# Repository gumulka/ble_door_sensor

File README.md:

# Bluetooth Window/Door Sensor

A simple project to observe a window or door is open/closed.
It works like most other sensors as well. A magnet has to get attached to the door and
if it comes near the board, it is detected and the state of the window or door is updated.

## How to build

If you are new to Zephyr, read the [Getting Started Guide](https://docs.zephyrproject.org/latest/develop/getting_started/index.html).
Afterwards you can clone and build this project with:

```bash
west init -m https://github.com/gumulka/ble_door_sensor --mr main door_sensor
cd door_sensor
west update
cd ble_door_sensor
```

### Bootloader

The bootloader will load and verify the image that is executed. To make it
easier to upgrade the device, two images are saved on the device and only one is
being executed, while the other is a standby for updating. The bootloader cannot
be upgraded via ble, but the image can be. Therefore making it possible to
upgrade devices in the field.

If you have a unprogrammed device, use this to build and flash the bootloader:

```bash
west build -p -b ble_door_sensor -d build_mcuboot ../bootloader/mcuboot/boot/zephyr/ -- -DCONFIG_BOOT_SIGNATURE_TYPE_ECDSA_P256=y
west flash -d build_mcuboot
```

### Application

The application is different from the bootloader and is what is in need of
updates/upgrades.

```bash
west build -p -b ble_door_sensor app
west flash
```

It is also possible to build the application with debug output for the UART
on the backside of the board.
This is disabled by default as it has a significant influence on battery.

```bash
west build -p -b ble_door_sensor app -- -DEXTRA_CONF_FILE=="debug.conf"
```

### Energy sensor

When I wanted to integrate energy consumption into home assistant without
having to order new hardware, I soldered two resistors to the board and
converted it into an energy monitor.
A 1M Ohm between VCC and AIN0 and 22k Ohm between AIN0 and GND.
This can be configured with:

```bash
west build -p -b ble_door_sensor app -- -DEXTRA_DTC_OVERLAY_FILE=="energy-tracker.dtsi"
```

## Update via BLE

If you have an already running device and just want to upgrade to the latest
firmware.

Either with the nRF Connect App, which can be quite handy, or in the commandline
use these steps:

```bash
sudo mcumgr --conntype ble --connstring ctlr_name=hci0,peer_name='Sensor' image upload build/zephyr/zephyr.signed.bin
sudo mcumgr --conntype ble --connstring ctlr_name=hci0,peer_name='Sensor' image list
```

Use the second hash provided from the second command to alter the following:

```bash
sudo mcumgr --conntype ble --connstring ctlr_name=hci0,peer_name='Sensor' image test "HASH_FROM_OUTPUT"
sudo mcumgr --conntype ble --connstring ctlr_name=hci0,peer_name='Sensor' reset
# wait for the system to restart and if you are sure, that the update was successful then
sudo mcumgr  --conntype ble --connstring ctlr_name=hci0,peer_name='Sensor' image confirm "HASH_FROM_OUTPUT"
```

More information about the general procedure can be found [here](https://docs.zephyrproject.org/latest/samples/subsys/mgmt/mcumgr/smp_svr/README.html)
and [here](https://docs.zephyrproject.org/latest/services/device_mgmt/mcumgr.html)

> [!TIP]
> I have seen a few errors when trying to upload the image and found that it
> works best, if I cancel the upload command after a few seconds and restart it
> a few seconds later, basically splitting the upload into 4-5 chunks instead
> of uploading it as a whole.

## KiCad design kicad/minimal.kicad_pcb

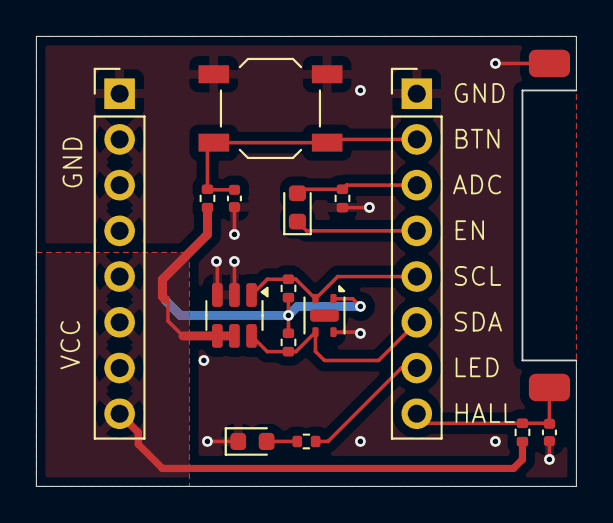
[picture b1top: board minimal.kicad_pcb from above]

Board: 2 copper layers, 30.0 x 25.0 mm, 16 parts (0 on the bottom side), 10 nets.

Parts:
C101: 10nF; C_0402_1005Metric
C102: 100nF; C_0402_1005Metric
D101: LED; LED_0603_1608Metric
J101, J102: Conn_01x08; PinHeader_1x08_P2.54mm_Vertical
Q101: ALS-PT19; LED_0603_1608Metric
R101, R106: 1K; R_0402_1005Metric
R102: 1M; R_0402_1005Metric
R103, R104, R105: 100k; R_0402_1005Metric
SW101: SW_Reed; reed_contact
SW102: SW_Push; SW_SPST_TL3342
U101: SHTC3; Sensirion_DFN-4-1EP_2x2mm_P1mm_EP0.7x1.6mm
U102: TMP100; SOT-23-6

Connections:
/BUTTON: C102.1, J102.2, R103.2, SW102.2
/HALL_SENSOR: C101.1, J102.8, R102.2, SW101.2
/LED: J102.7, R101.1
/PHOTO_ADC: J102.3, Q101.2 (E), R106.1
/PHOTO_ENABLE: J102.4, Q101.1 (C)
/SCL: J102.5, R104.2, U101.2 (SCL), U102.1 (SCL)
/SDA: J102.6, R105.2, U101.3 (SDA), U102.6 (SDA)
GND: C101.2, C102.2, D101.1 (K), J101.1, J101.2, J101.3, J101.4, J102.1, R106.2, SW101.1, SW102.1, U101.4 (VSS), U102.2 (GND), U102.3 (ADD1)
unnamed: D101.2 (A), R101.2
VCC: J101.5, J101.6, J101.7, J101.8, R102.1, R103.1, R104.1, R105.1, U101.1 (VDD), U102.4 (V+), U102.5 (ADD0)

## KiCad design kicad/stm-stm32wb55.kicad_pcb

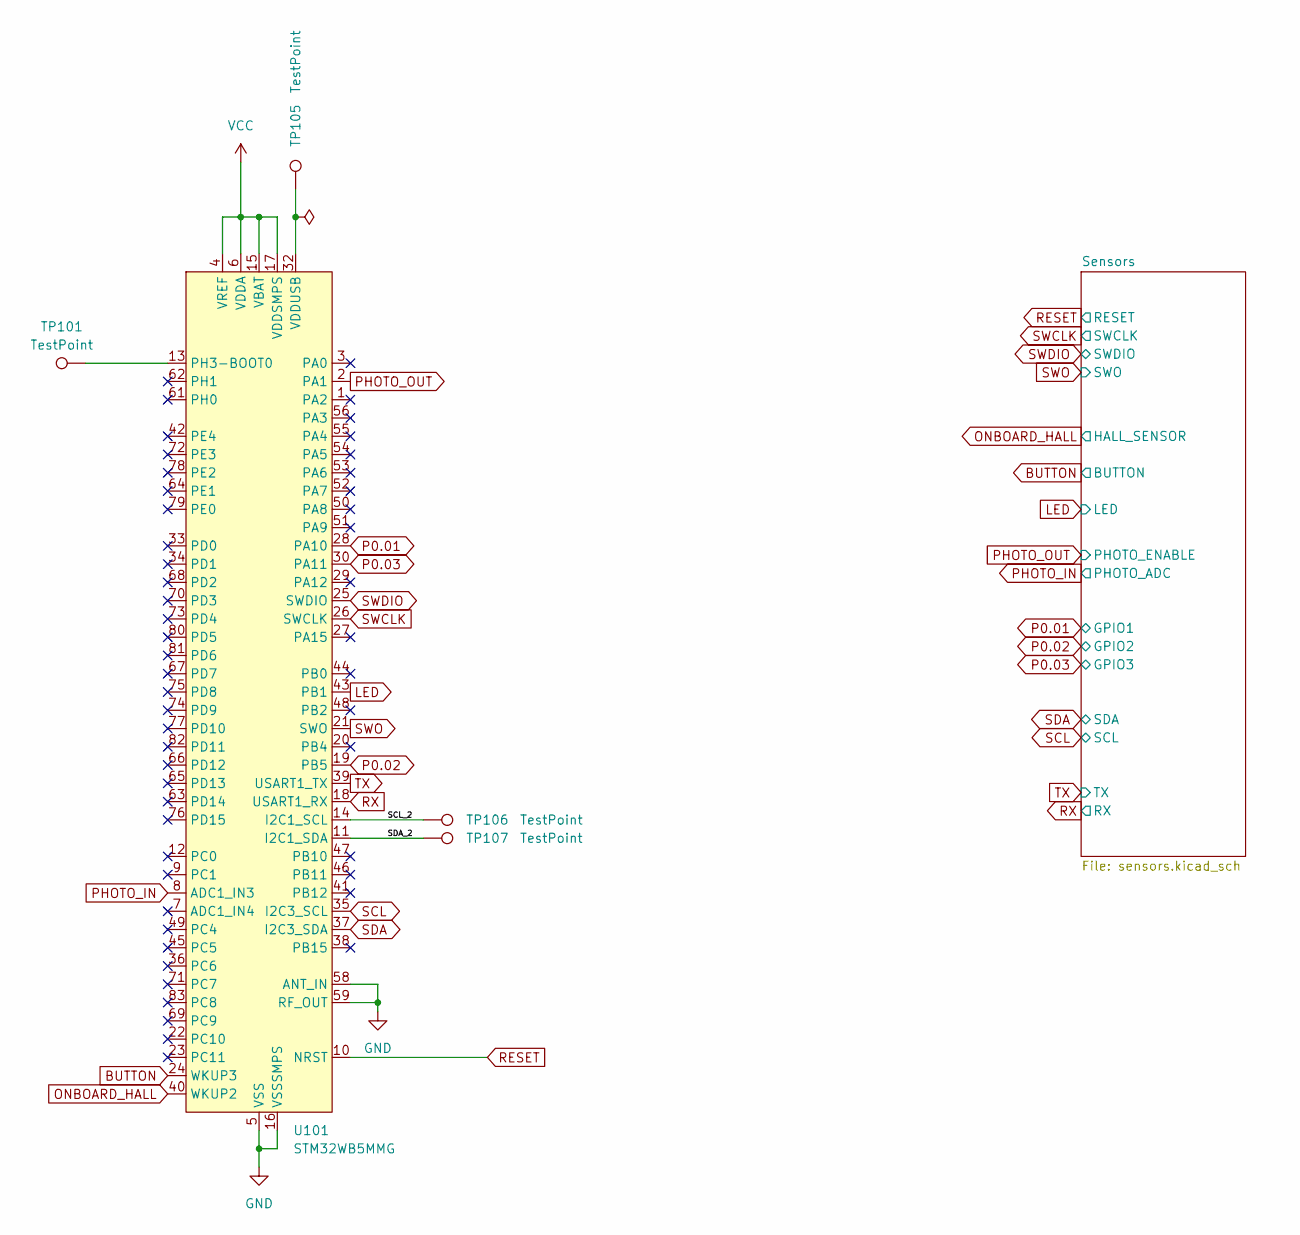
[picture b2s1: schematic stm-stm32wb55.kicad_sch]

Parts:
TP101, TP105, TP106, TP107: TestPoint; TestPoint_Pad_D1.5mm
U101: STM32WB5MMG; ST-SiP-LGA-86-11x7.3mm

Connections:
/SCL_2: TP106.1, U101.14 (I2C1_SCL)
/SDA_2: TP107.1, U101.11 (I2C1_SDA)
BUTTON: U101.24 (WKUP3); also elsewhere on the board
GND: U101.5 (VSS), U101.16 (VSSSMPS), U101.31 (VSS), U101.57 (VSS), U101.58 (ANT_IN), U101.59 (RF_OUT), U101.60 (VSS), U101.84 (VSS), U101.86 (VSS); also elsewhere on the board
LED: U101.43 (PB1); also elsewhere on the board
unnamed: TP101.1, U101.13 (PH3-BOOT0)
unnamed: TP105.1, U101.32 (VDDUSB)
ONBOARD_HALL: U101.40 (WKUP2); also elsewhere on the board
P0.01: U101.28 (PA10); also elsewhere on the board
P0.02: U101.19 (PB5); also elsewhere on the board
P0.03: U101.30 (PA11); also elsewhere on the board
PHOTO_IN: U101.8 (ADC1_IN3); also elsewhere on the board
PHOTO_OUT: U101.2 (PA1); also elsewhere on the board
RESET: U101.10 (NRST); also elsewhere on the board
RX: U101.18 (USART1_RX); also elsewhere on the board
SCL: U101.35 (I2C3_SCL); also elsewhere on the board
SDA: U101.37 (I2C3_SDA); also elsewhere on the board
SWCLK: U101.26 (SWCLK); also elsewhere on the board
SWDIO: U101.25 (SWDIO); also elsewhere on the board
SWO: U101.21 (SWO); also elsewhere on the board
TX: U101.39 (USART1_TX); also elsewhere on the board
VCC: U101.4 (VREF), U101.6 (VDDA), U101.15 (VBAT), U101.17 (VDDSMPS); also elsewhere on the board

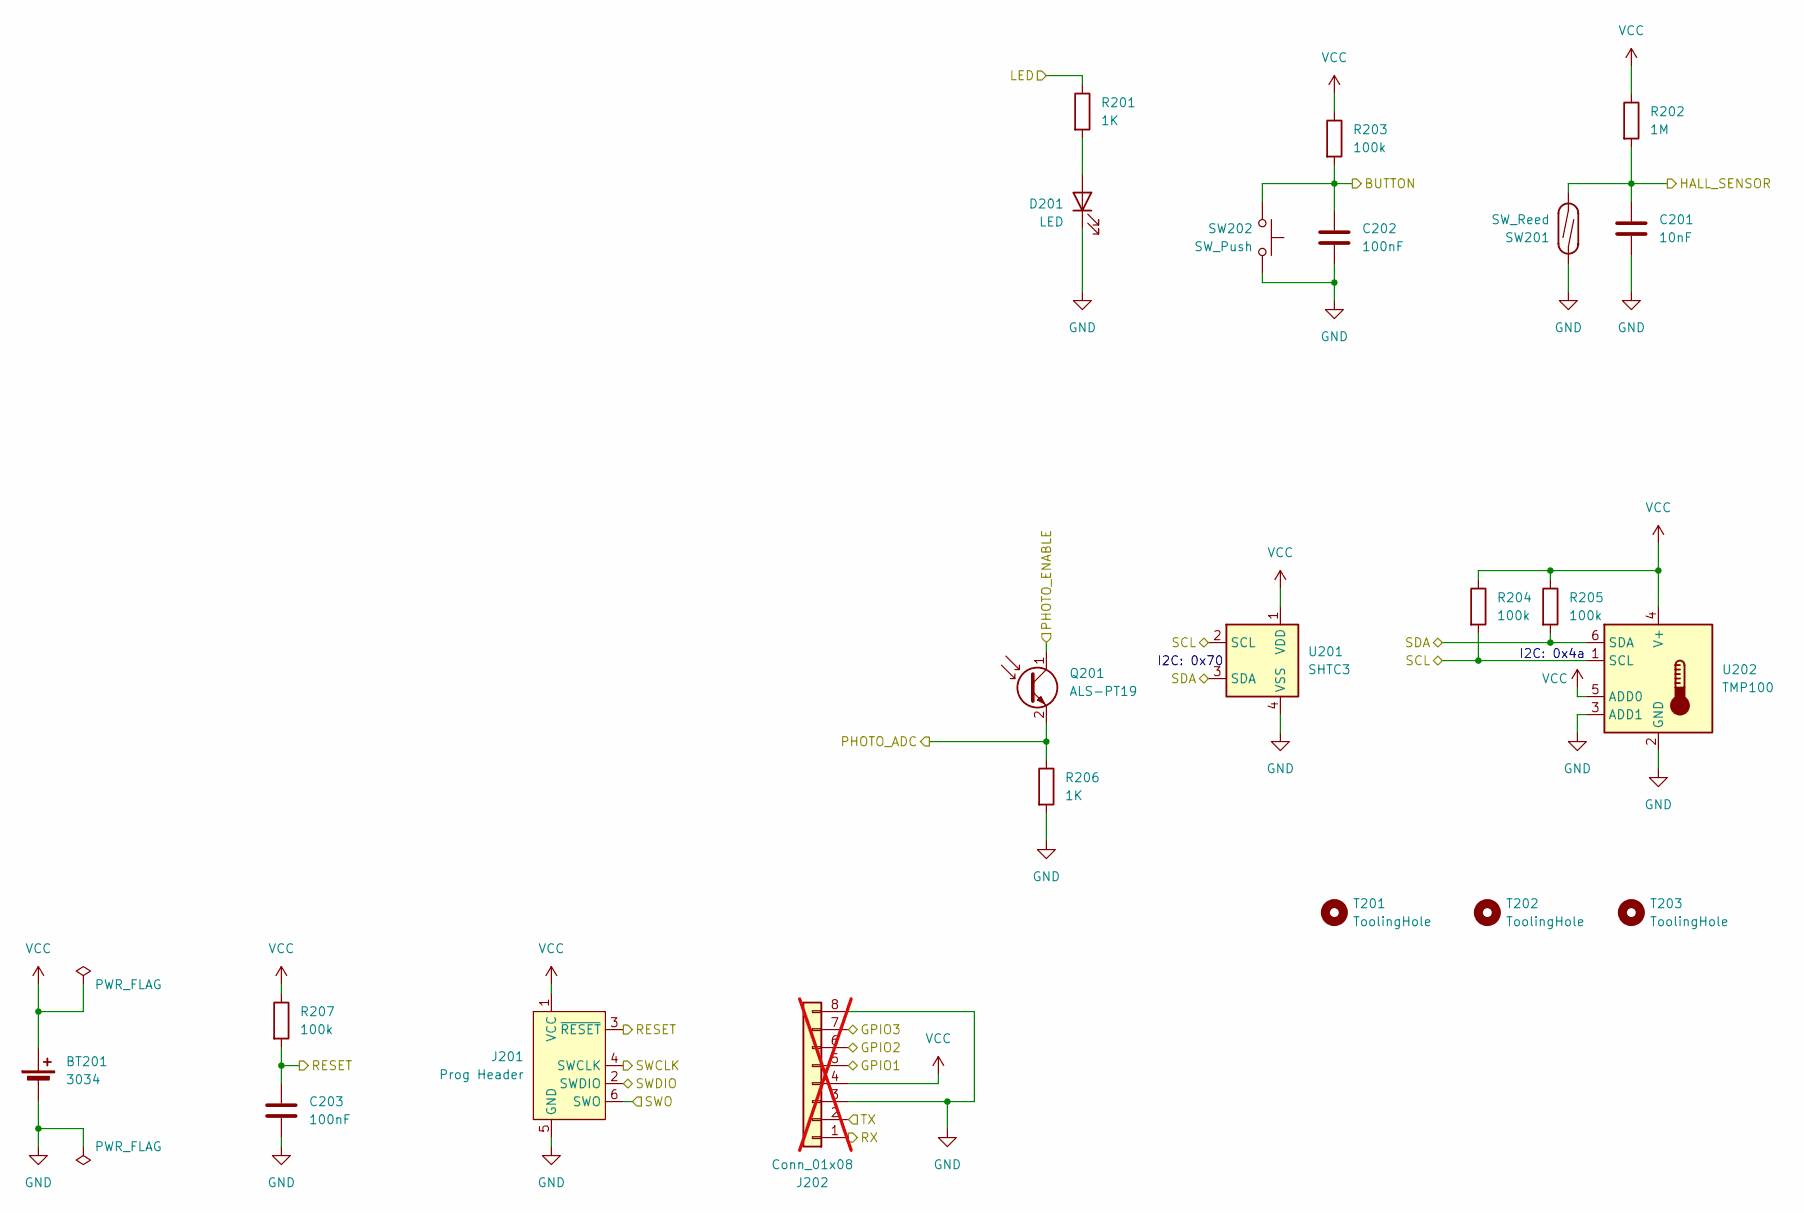
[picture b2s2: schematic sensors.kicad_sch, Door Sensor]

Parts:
BT201: 3034; BatteryHolder_Keystone_3034_1x20mm; MPN 3034TR; LCSC# C5213768
C201: 10nF; C_0402_1005Metric; MPN 10nF 0402; LCSC# C15195
C202, C203: 100nF; C_0402_1005Metric; MPN 100nF 0402; LCSC# C1525
D201: LED; LED_0603_1608Metric; MPN KP-1608SGC; LCSC# C72043
J201: Prog Header; Tag-Connect_TC2030-IDC-NL_2x03_P1.27mm_Vertical
J202: Conn_01x08; PinHeader_1x08_P2.54mm_Vertical_SMD_Pin1Left; not fitted
Q201: ALS-PT19; LED_0603_1608Metric; MPN ALS-PT19-315C/L177/TR8; LCSC# C146233
R201, R206: 1K; R_0402_1005Metric; MPN 1K; LCSC# C11702
R202: 1M; R_0402_1005Metric; MPN 1M; LCSC# C26083
R203, R204, R205, R207: 100k; R_0402_1005Metric; MPN 100K; LCSC# C25741
SW201: SW_Reed; reed_contact
SW202: SW_Push; SW_SPST_TL3342; MPN TS-1187A-B-A-B; LCSC# C318884
T201, T202, T203: ToolingHole; JLCPCB_Mounting_hole
U201: SHTC3; Sensirion_DFN-4-1EP_2x2mm_P1mm_EP0.7x1.6mm; MPN SHTC3-TR-10KS; LCSC# C2880044
U202: TMP100; SOT-23-6; MPN TMP100NA/3K; LCSC# C31810

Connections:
BUTTON: C202.1, R203.2, SW202.2; also elsewhere on the board
GND: BT201.2 (-), C201.2, C202.2, C203.2, D201.1 (K), J201.5 (GND), J202.3, J202.8, R206.2, SW201.2, SW202.1, U201.4 (VSS), U202.2 (GND), U202.3 (ADD1); also elsewhere on the board
LED: R201.1; also elsewhere on the board
unnamed: D201.2 (A), R201.2
ONBOARD_HALL: C201.1, R202.2, SW201.1; also elsewhere on the board
P0.01: J202.5; also elsewhere on the board
P0.02: J202.6; also elsewhere on the board
P0.03: J202.7; also elsewhere on the board
PHOTO_IN: Q201.2 (E), R206.1; also elsewhere on the board
PHOTO_OUT: Q201.1 (C); also elsewhere on the board
RESET: C203.1, J201.3 (~RESET), R207.2; also elsewhere on the board
RX: J202.1; also elsewhere on the board
SCL: R204.2, U201.2 (SCL), U202.1 (SCL); also elsewhere on the board
SDA: R205.2, U201.3 (SDA), U202.6 (SDA); also elsewhere on the board
SWCLK: J201.4 (SWCLK); also elsewhere on the board
SWDIO: J201.2 (SWDIO); also elsewhere on the board
SWO: J201.6 (SWO); also elsewhere on the board
TX: J202.2; also elsewhere on the board
VCC: BT201.1 (+), J201.1 (VCC), J202.4, R202.1, R203.1, R204.1, R205.1, R207.1, U201.1 (VDD), U202.4 (V+), U202.5 (ADD0); also elsewhere on the board

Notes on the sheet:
I2C: 0x4a
I2C: 0x70

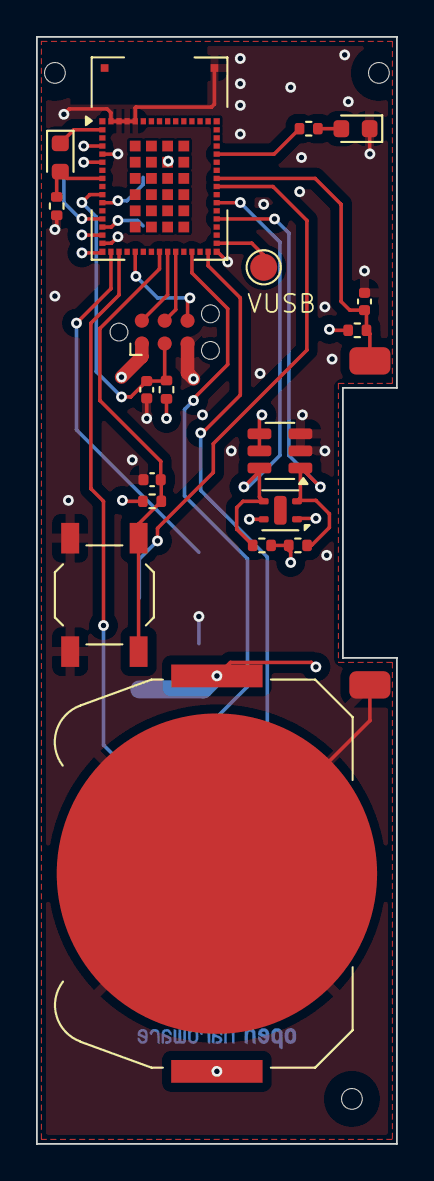
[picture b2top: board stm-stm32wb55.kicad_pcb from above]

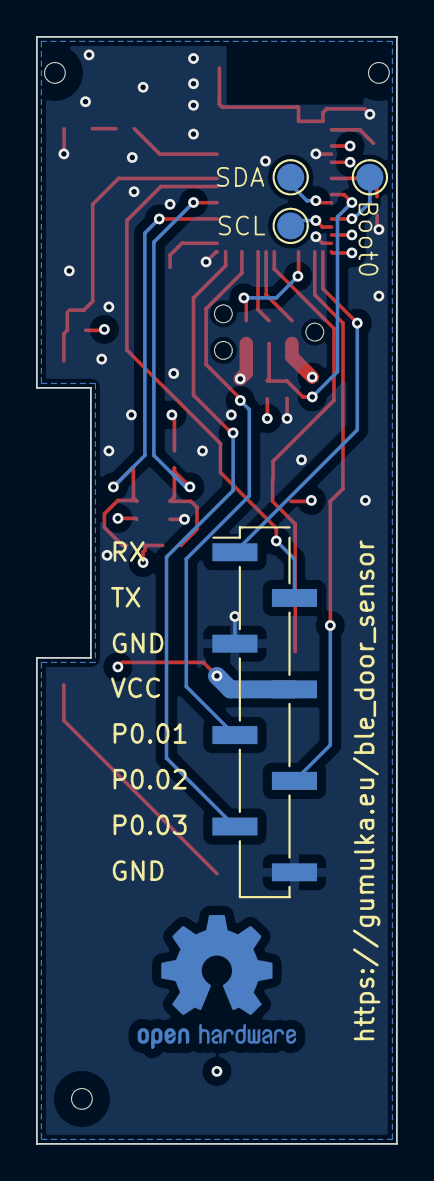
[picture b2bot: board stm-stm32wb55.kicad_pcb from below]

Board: 4 copper layers, 20.0 x 61.5 mm, 27 parts (4 on the bottom side), 23 nets.

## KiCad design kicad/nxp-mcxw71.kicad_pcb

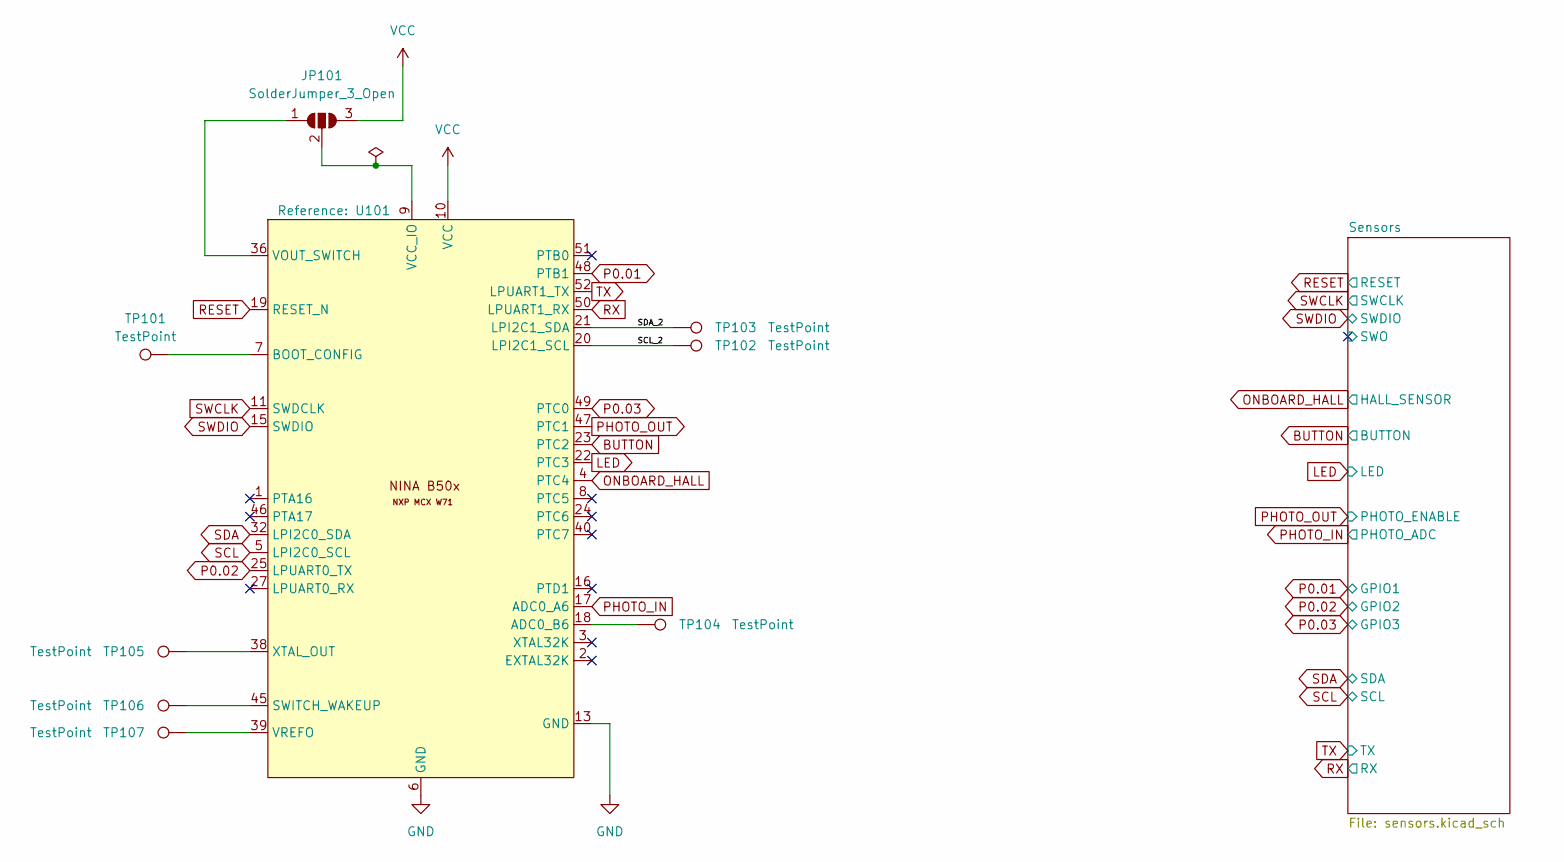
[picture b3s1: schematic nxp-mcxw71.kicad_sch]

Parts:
JP101: SolderJumper_3_Open; SolderJumper-3_P2.0mm_Open_TrianglePad1.0x1.5mm
TP101, TP102, TP103, TP104, TP105, TP106, TP107: TestPoint; TestPoint_Pad_D1.5mm
U101: NINA-B506

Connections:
/SCL_2: TP102.1, U101.20 (LPI2C1_SCL)
/SDA_2: TP103.1, U101.21 (LPI2C1_SDA)
BUTTON: U101.23 (PTC2); also elsewhere on the board
GND: U101.6 (GND), U101.12 (GND), U101.13 (GND), U101.14 (GND), U101.26 (GND), U101.30 (GND), U101.53 (GND), U101.EGP (GND); also elsewhere on the board
LED: U101.22 (PTC3); also elsewhere on the board
unnamed: JP101.1 (A), U101.36 (VOUT_SWITCH)
unnamed: JP101.2 (C), U101.9 (VCC_IO)
unnamed: TP101.1, U101.7 (BOOT_CONFIG)
unnamed: TP104.1, U101.18 (ADC0_B6)
unnamed: TP106.1, U101.45 (SWITCH_WAKEUP)
unnamed: TP107.1, U101.39 (VREFO)
unnamed: TP105.1, U101.38 (XTAL_OUT)
ONBOARD_HALL: U101.4 (PTC4); also elsewhere on the board
P0.01: U101.48 (PTB1); also elsewhere on the board
P0.02: U101.25 (LPUART0_TX); also elsewhere on the board
P0.03: U101.49 (PTC0); also elsewhere on the board
PHOTO_IN: U101.17 (ADC0_A6); also elsewhere on the board
PHOTO_OUT: U101.47 (PTC1); also elsewhere on the board
RESET: U101.19 (RESET_N); also elsewhere on the board
RX: U101.50 (LPUART1_RX); also elsewhere on the board
SCL: U101.5 (LPI2C0_SCL); also elsewhere on the board
SDA: U101.32 (LPI2C0_SDA); also elsewhere on the board
SWCLK: U101.11 (SWDCLK); also elsewhere on the board
SWDIO: U101.15 (SWDIO); also elsewhere on the board
TX: U101.52 (LPUART1_TX); also elsewhere on the board
VCC: JP101.3 (B), U101.10 (VCC); also elsewhere on the board

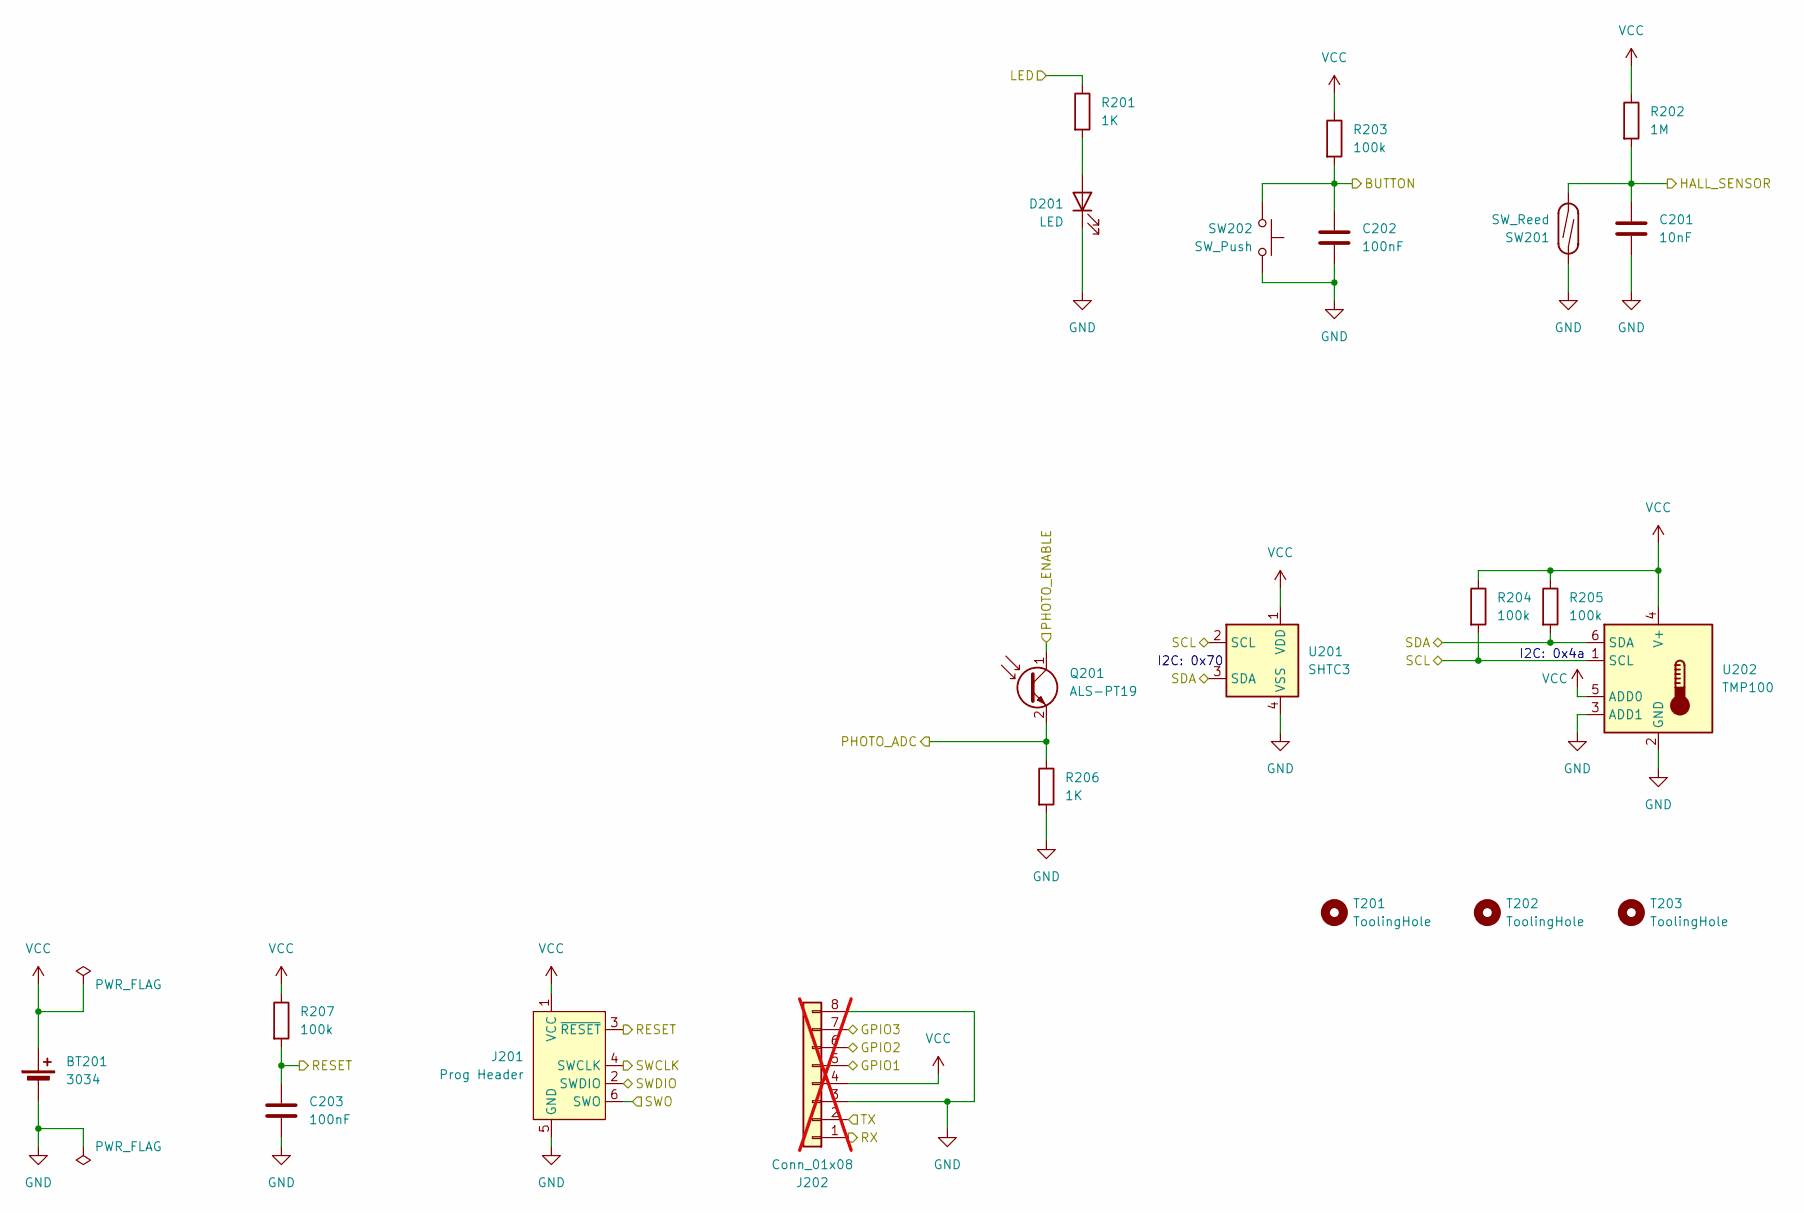
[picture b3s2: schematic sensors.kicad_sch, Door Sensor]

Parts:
BT201: 3034; BatteryHolder_Keystone_3034_1x20mm; MPN 3034TR; LCSC# C5213768
C201: 10nF; C_0402_1005Metric; MPN 10nF 0402; LCSC# C15195
C202, C203: 100nF; C_0402_1005Metric; MPN 100nF 0402; LCSC# C1525
D201: LED; LED_0603_1608Metric; MPN KP-1608SGC; LCSC# C72043
J201: Prog Header; Tag-Connect_TC2030-IDC-NL_2x03_P1.27mm_Vertical
J202: Conn_01x08; PinHeader_1x08_P2.54mm_Vertical_SMD_Pin1Left; not fitted
Q201: ALS-PT19; LED_0603_1608Metric; MPN ALS-PT19-315C/L177/TR8; LCSC# C146233
R201, R206: 1K; R_0402_1005Metric; MPN 1K; LCSC# C11702
R202: 1M; R_0402_1005Metric; MPN 1M; LCSC# C26083
R203, R204, R205, R207: 100k; R_0402_1005Metric; MPN 100K; LCSC# C25741
SW201: SW_Reed; reed_contact
SW202: SW_Push; SW_SPST_TL3342; MPN TS-1187A-B-A-B; LCSC# C318884
T201, T202, T203: ToolingHole; JLCPCB_Mounting_hole
U201: SHTC3; Sensirion_DFN-4-1EP_2x2mm_P1mm_EP0.7x1.6mm; MPN SHTC3-TR-10KS; LCSC# C2880044
U202: TMP100; SOT-23-6; MPN TMP100NA/3K; LCSC# C31810

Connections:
/Sensors/SWO: J201.6 (SWO)
BUTTON: C202.1, R203.2, SW202.2; also elsewhere on the board
GND: BT201.2 (-), C201.2, C202.2, C203.2, D201.1 (K), J201.5 (GND), J202.3, J202.8, R206.2, SW201.2, SW202.1, U201.4 (VSS), U202.2 (GND), U202.3 (ADD1); also elsewhere on the board
LED: R201.1; also elsewhere on the board
unnamed: D201.2 (A), R201.2
ONBOARD_HALL: C201.1, R202.2, SW201.1; also elsewhere on the board
P0.01: J202.5; also elsewhere on the board
P0.02: J202.6; also elsewhere on the board
P0.03: J202.7; also elsewhere on the board
PHOTO_IN: Q201.2 (E), R206.1; also elsewhere on the board
PHOTO_OUT: Q201.1 (C); also elsewhere on the board
RESET: C203.1, J201.3 (~RESET), R207.2; also elsewhere on the board
RX: J202.1; also elsewhere on the board
SCL: R204.2, U201.2 (SCL), U202.1 (SCL); also elsewhere on the board
SDA: R205.2, U201.3 (SDA), U202.6 (SDA); also elsewhere on the board
SWCLK: J201.4 (SWCLK); also elsewhere on the board
SWDIO: J201.2 (SWDIO); also elsewhere on the board
TX: J202.2; also elsewhere on the board
VCC: BT201.1 (+), J201.1 (VCC), J202.4, R202.1, R203.1, R204.1, R205.1, R207.1, U201.1 (VDD), U202.4 (V+), U202.5 (ADD0); also elsewhere on the board

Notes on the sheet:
I2C: 0x4a
I2C: 0x70

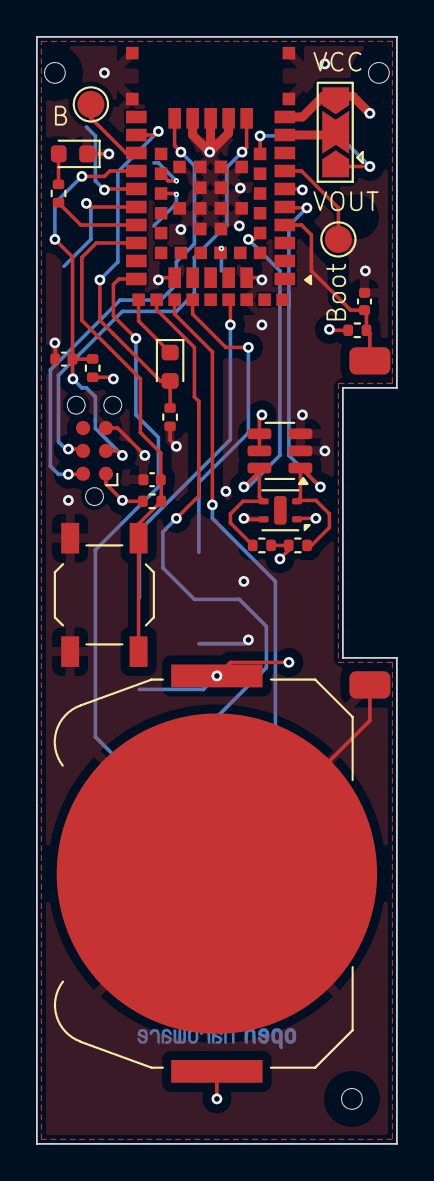
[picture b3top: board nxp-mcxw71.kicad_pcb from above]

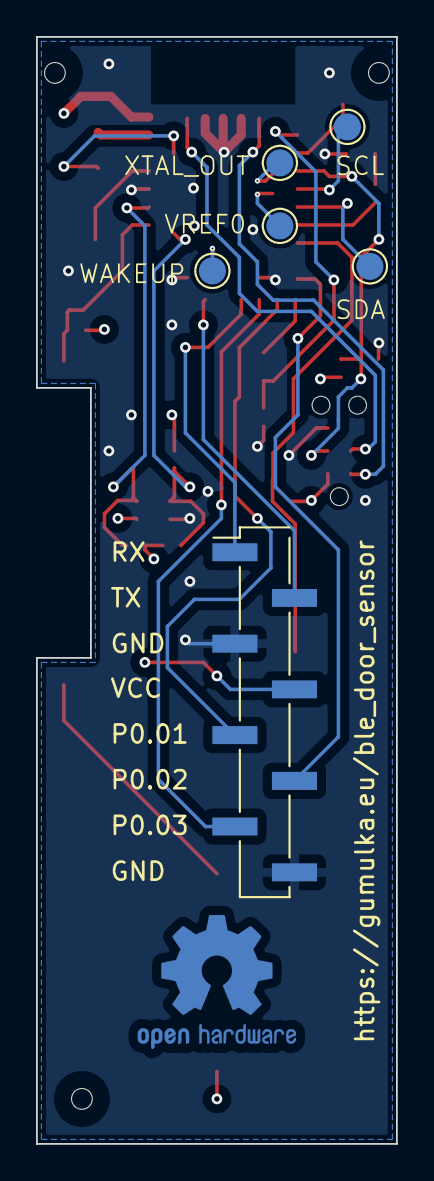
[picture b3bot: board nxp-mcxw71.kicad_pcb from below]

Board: 4 copper layers, 20.0 x 61.5 mm, 31 parts (6 on the bottom side), 27 nets.

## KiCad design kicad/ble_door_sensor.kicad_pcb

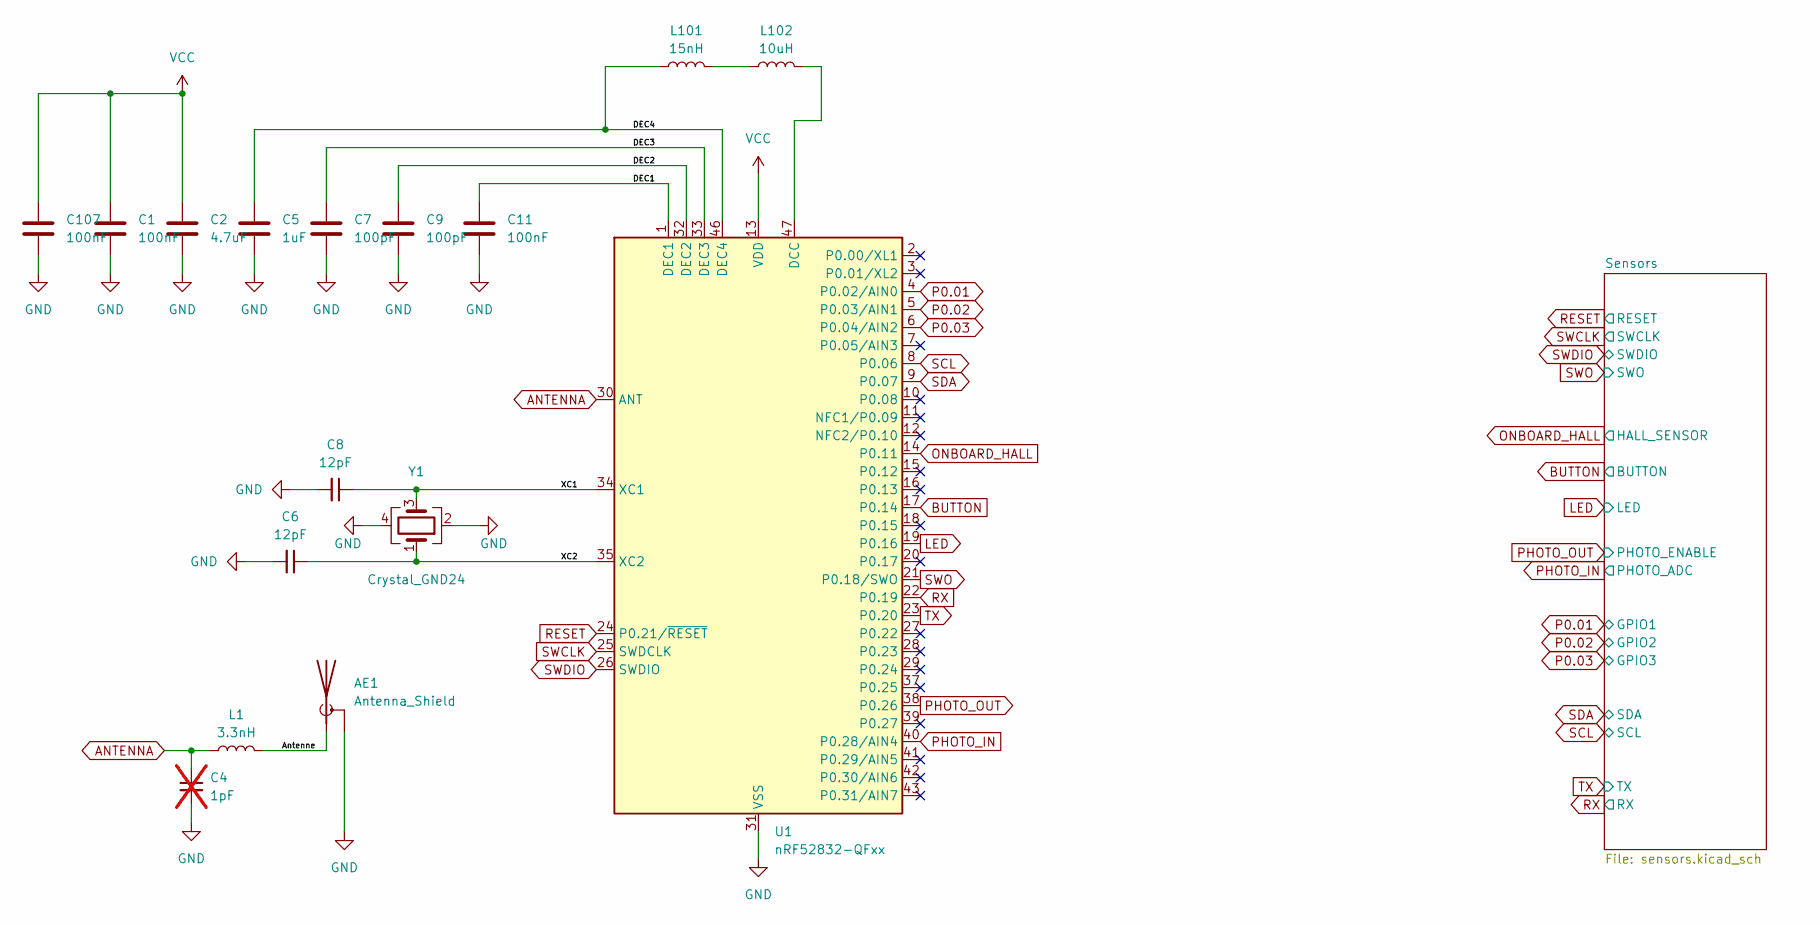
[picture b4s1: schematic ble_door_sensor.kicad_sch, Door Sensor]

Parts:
AE1: Antenna_Shield; Texas_SWRA117D_2.4GHz_Right
C1, C11, C107: 100nF; C_0402_1005Metric; MPN 100nF 0402; LCSC# C1525
C2: 4.7uF; C_0603_1608Metric; MPN 4,7uF 0603; LCSC# C19666
C4: 1pF; C_0402_1005Metric; not fitted
C5: 1uF; C_0603_1608Metric; MPN 1uF 0603; LCSC# C15849
C6, C8: 12pF; C_0402_1005Metric; MPN 12pF 0402; LCSC# C1547
C7, C9: 100pF; C_0402_1005Metric; MPN 100pF 0402; LCSC# C1546
L1: 3.3nH; L_0402_1005Metric; MPN LQG15HS3N3C02D; LCSC# C14033
L101: 15nH; L_0402_1005Metric; MPN LQW15AN15NH00D; LCSC# C27143
L102: 10uH; L_0603_1608Metric; MPN MLZ1608E100MT; LCSC# C1035
U1: nRF52832-QFxx; QFN-48-1EP_6x6mm_P0.4mm_EP4.6x4.6mm; MPN NRF52832-QFAA-R; LCSC# C77540
Y1: Crystal_GND24; Crystal_SMD_3225-4Pin_3.2x2.5mm; MPN X322532MOB4SI; LCSC# C9009

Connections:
/Antenne: AE1.1 (A), L1.2
/DEC1: C11.1, U1.1 (DEC1)
/DEC2: C9.1, U1.32 (DEC2)
/DEC3: C7.1, U1.33 (DEC3)
/DEC4: C5.1, L101.1, U1.46 (DEC4)
/Photo_in: U1.40 (P0.28/AIN4); also elsewhere on the board
/Photo_out: U1.38 (P0.26); also elsewhere on the board
/XC1: C8.1, U1.34 (XC1), Y1.3
/XC2: C6.1, U1.35 (XC2), Y1.1
ANTENNA: C4.1, L1.1, U1.30 (ANT)
BUTTON: U1.17 (P0.14); also elsewhere on the board
GND: AE1.2 (Shield), C1.2, C2.2, C4.2, C5.2, C6.2, C7.2, C8.2, C9.2, C11.2, C107.2, U1.31 (VSS), U1.45 (VSS), U1.49 (VSS), Y1.2, Y1.4; also elsewhere on the board
LED: U1.19 (P0.16); also elsewhere on the board
unnamed: L101.2, L102.1
unnamed: L102.2, U1.47 (DCC)
ONBOARD_HALL: U1.14 (P0.11); also elsewhere on the board
P0.01: U1.4 (P0.02/AIN0); also elsewhere on the board
P0.02: U1.5 (P0.03/AIN1); also elsewhere on the board
P0.03: U1.6 (P0.04/AIN2); also elsewhere on the board
RESET: U1.24 (P0.21/~RESET); also elsewhere on the board
RX: U1.22 (P0.19); also elsewhere on the board
SWCLK: U1.25 (SWDCLK); also elsewhere on the board
SWDIO: U1.26 (SWDIO); also elsewhere on the board
SWO: U1.21 (P0.18/SWO); also elsewhere on the board
TX: U1.23 (P0.20); also elsewhere on the board
VCC: C1.1, C2.1, C107.1, U1.13 (VDD), U1.36 (VDD), U1.48 (VDD); also elsewhere on the board

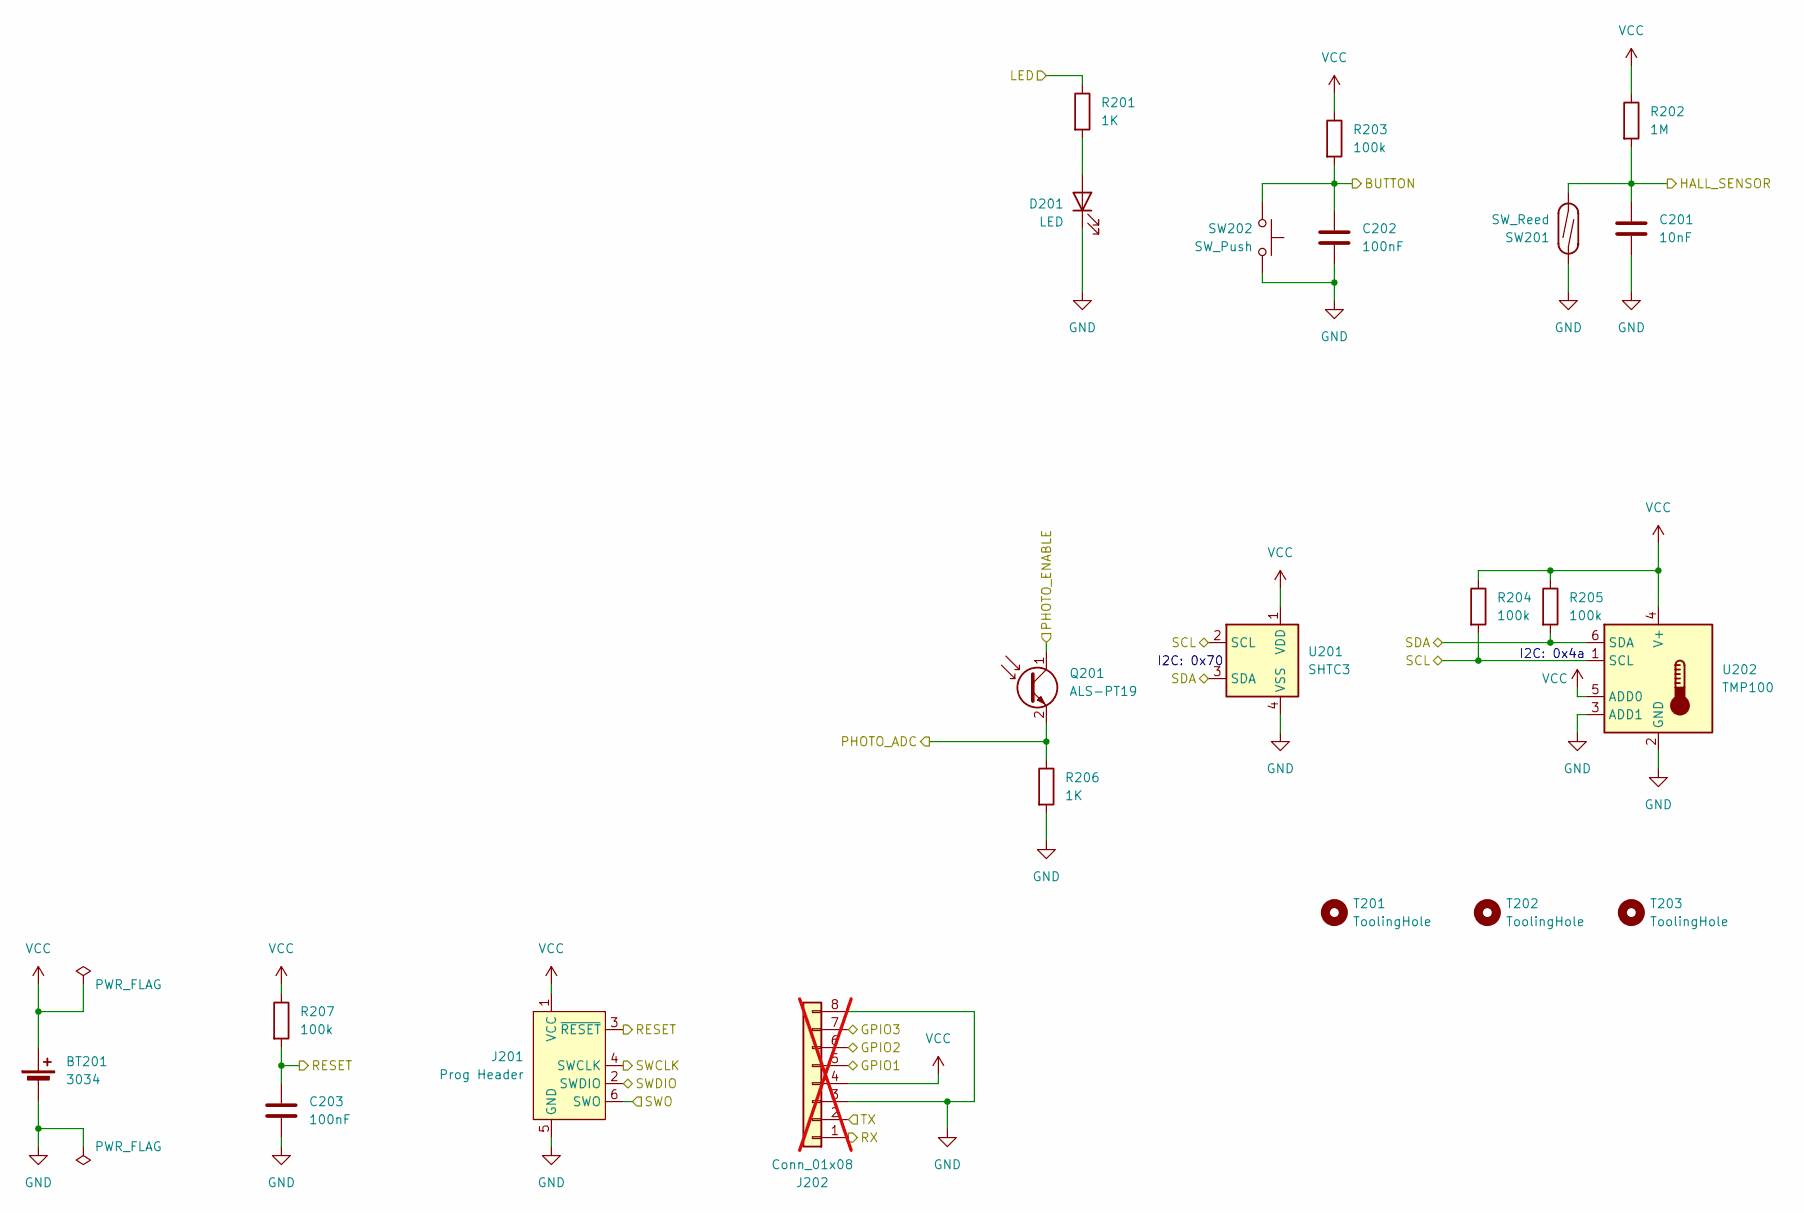
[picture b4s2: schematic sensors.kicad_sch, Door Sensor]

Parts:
BT201: 3034; BatteryHolder_Keystone_3034_1x20mm; MPN 3034TR; LCSC# C5213768
C201: 10nF; C_0402_1005Metric; MPN 10nF 0402; LCSC# C15195
C202, C203: 100nF; C_0402_1005Metric; MPN 100nF 0402; LCSC# C1525
D201: LED; LED_0603_1608Metric; MPN KP-1608SGC; LCSC# C72043
J201: Prog Header; Tag-Connect_TC2030-IDC-NL_2x03_P1.27mm_Vertical
J202: Conn_01x08; PinHeader_1x08_P2.54mm_Vertical_SMD_Pin1Left; not fitted
Q201: ALS-PT19; LED_0603_1608Metric; MPN ALS-PT19-315C/L177/TR8; LCSC# C146233
R201, R206: 1K; R_0402_1005Metric; MPN 1K; LCSC# C11702
R202: 1M; R_0402_1005Metric; MPN 1M; LCSC# C26083
R203, R204, R205, R207: 100k; R_0402_1005Metric; MPN 100K; LCSC# C25741
SW201: SW_Reed; reed_contact
SW202: SW_Push; SW_SPST_TL3342; MPN TS-1187A-B-A-B; LCSC# C318884
T201, T202, T203: ToolingHole; JLCPCB_Mounting_hole
U201: SHTC3; Sensirion_DFN-4-1EP_2x2mm_P1mm_EP0.7x1.6mm; MPN SHTC3-TR-10KS; LCSC# C2880044
U202: TMP100; SOT-23-6; MPN TMP100NA/3K; LCSC# C31810

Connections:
/Photo_in: Q201.2 (E), R206.1; also elsewhere on the board
/Photo_out: Q201.1 (C); also elsewhere on the board
BUTTON: C202.1, R203.2, SW202.2; also elsewhere on the board
GND: BT201.2 (-), C201.2, C202.2, C203.2, D201.1 (K), J201.5 (GND), J202.3, J202.8, R206.2, SW201.2, SW202.1, U201.4 (VSS), U202.2 (GND), U202.3 (ADD1); also elsewhere on the board
LED: R201.1; also elsewhere on the board
unnamed: D201.2 (A), R201.2
ONBOARD_HALL: C201.1, R202.2, SW201.1; also elsewhere on the board
P0.01: J202.5; also elsewhere on the board
P0.02: J202.6; also elsewhere on the board
P0.03: J202.7; also elsewhere on the board
RESET: C203.1, J201.3 (~RESET), R207.2; also elsewhere on the board
RX: J202.1; also elsewhere on the board
SWCLK: J201.4 (SWCLK); also elsewhere on the board
SWDIO: J201.2 (SWDIO); also elsewhere on the board
SWO: J201.6 (SWO); also elsewhere on the board
TX: J202.2; also elsewhere on the board
VCC: BT201.1 (+), J201.1 (VCC), J202.4, R202.1, R203.1, R204.1, R205.1, R207.1, U201.1 (VDD), U202.4 (V+), U202.5 (ADD0); also elsewhere on the board

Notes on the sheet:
I2C: 0x4a
I2C: 0x70

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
